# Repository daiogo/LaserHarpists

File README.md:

# What is a laser harp?
A laser harp is a harp that has laser beams emulating the strings of a regular harp. Whenever you intercept a laser beam, a note is played to that correspondent intercepted beam.

# Cool features in our laser harp
- The notes are played by an Android app;
- It's wireless! It communicates with the app via Bluetooth;
- There are ultrasonic range finders that measure the height of your interception;
  - That makes it possible to play 3 notes in a single laser beam.
- There are two modes of operation:
  - Free Play: let your inner Jean Michel Jarre shine (:
  - Learn To Play: learn to play a song in the harp
- RGB LED strips positioned in the front of each laser beam
  - They lit to the note you play when you intercept a laser beam on Free Play mode
  - They lit to the correspondent string and height to be intercepted in the current music

# Pics or it didn't happen
Yes, there's a demo video! Too bad we didn't had the time to learn how to play the harp (:

https://www.youtube.com/watch?v=IKeanOgFvdw

# Bill of materials
- Tiva C Launchpad
- JY-MCU Bluetooth module
- 8 HC-SR04 ultrasonic range finders
- 8 5mW laser diodes
- 8 interception sensors (circuit schematic found inside the repo)
  - comparator IC
  - potentiometer
  - LDR (Light dependent resistor)
  - 0.25W resistors
  - Materials to build a PCB to each interception sensor
- 8 12V RGB LED strips
- 3 high current drivers IC
- 3 shift registers

# Makers
- José Augustinho
  - Firmware programming, PCB confection and project manager
- Rinaldi Segecin
  - Mobile app development, firmware programming
- Diogo Freitas (myself)
  - Hardware development, PCB confection, firmware debugging

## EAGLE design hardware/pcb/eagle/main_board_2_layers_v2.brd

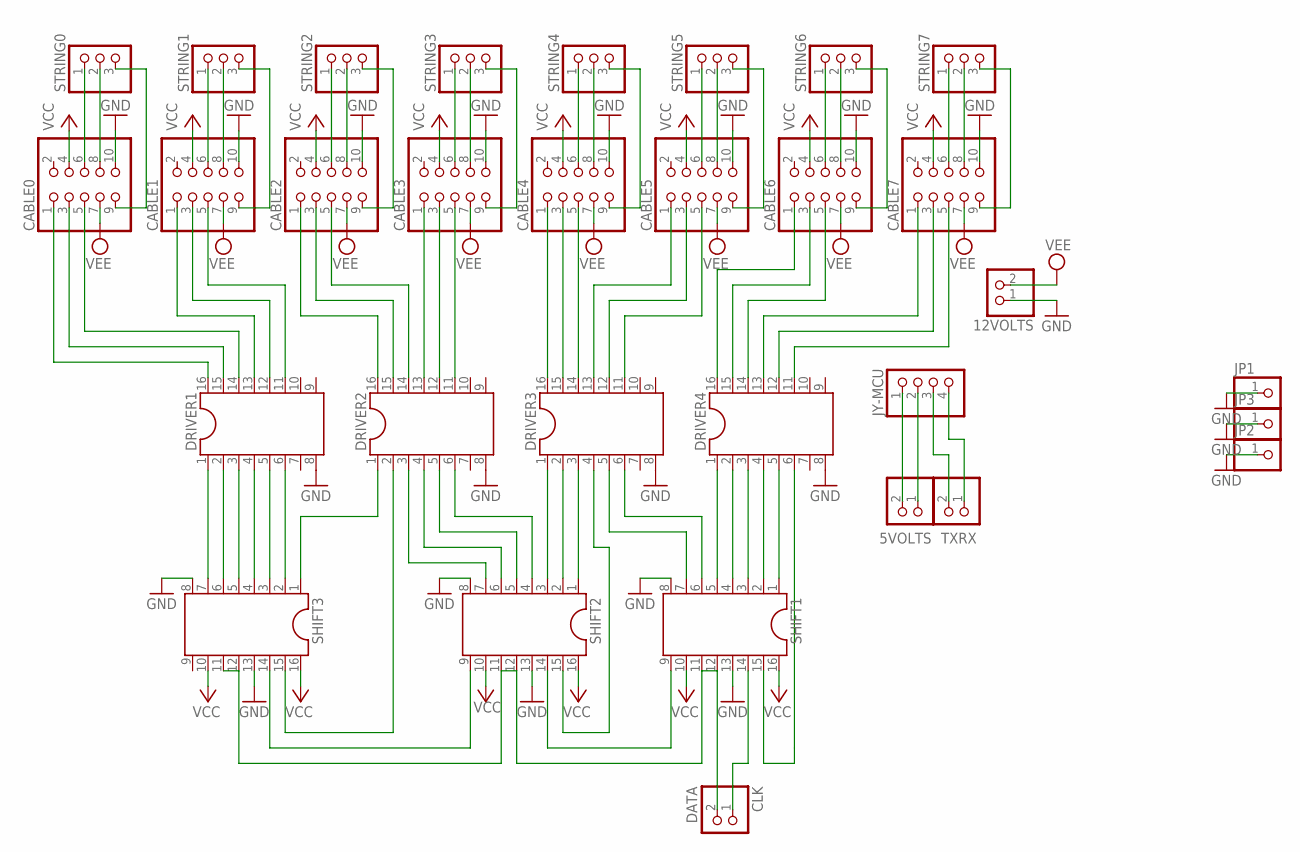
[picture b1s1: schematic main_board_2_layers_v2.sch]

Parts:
5VOLTS, 12VOLTS: PINHD-1X2; 1X02
CABLE0, CABLE1, CABLE2, CABLE3, CABLE4, CABLE5, CABLE6, CABLE7: PINHD-2X5; 2X05
CLK: DATA; 1X02
DRIVER1, DRIVER2, DRIVER3, DRIVER4: DIL16
JP1, JP2, JP3: PINHD-1X1; 1X01
JY-MCU: PINHD-1X4; 1X04
SHIFT1, SHIFT2, SHIFT3: DIL16
STRING0, STRING1, STRING2, STRING3, STRING4, STRING5, STRING6, STRING7: PINHD-1X3; 1X03
TXRX: PINHD-1X2; 1X02

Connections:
GND: 12VOLTS.1, CABLE0.10, CABLE1.10, CABLE2.10, CABLE3.10, CABLE4.10, CABLE5.10, CABLE6.10, CABLE7.10, DRIVER1.8, DRIVER2.8, DRIVER3.8, DRIVER4.8, JP1.1, JP2.1, JP3.1, SHIFT1.8, SHIFT1.13, SHIFT2.8, SHIFT2.13, SHIFT3.8, SHIFT3.13
unnamed: CABLE0.1, DRIVER1.16
unnamed: CABLE0.3, DRIVER1.15
unnamed: CABLE0.5, DRIVER1.14
unnamed: CABLE1.1, DRIVER1.13
unnamed: CABLE1.3, DRIVER1.12
unnamed: CABLE1.5, DRIVER1.11
unnamed: CABLE2.1, DRIVER2.16
unnamed: CABLE2.3, DRIVER2.15
unnamed: CABLE2.5, DRIVER2.14
unnamed: CABLE3.1, DRIVER2.13
unnamed: CABLE3.3, DRIVER2.12
unnamed: CABLE3.5, DRIVER2.11
unnamed: CABLE4.1, DRIVER3.16
unnamed: CABLE4.3, DRIVER3.15
unnamed: CABLE4.5, DRIVER3.14
unnamed: CABLE5.1, DRIVER3.13
unnamed: CABLE5.3, DRIVER3.12
unnamed: CABLE5.5, DRIVER3.11
unnamed: CABLE6.1, DRIVER4.16
unnamed: CABLE6.3, DRIVER4.15
unnamed: CABLE7.1, DRIVER4.13
unnamed: CABLE6.5, DRIVER4.14
unnamed: CABLE7.3, DRIVER4.12
unnamed: CABLE7.5, DRIVER4.11
unnamed: DRIVER4.5, SHIFT1.1
unnamed: DRIVER4.4, SHIFT1.2
unnamed: CABLE1.9, STRING1.3
unnamed: CABLE0.6, STRING0.1
unnamed: CABLE0.9, STRING0.3
unnamed: CABLE0.8, STRING0.2
unnamed: CABLE7.6, STRING7.1
unnamed: CABLE7.8, STRING7.2
unnamed: CABLE1.6, STRING1.1
unnamed: CABLE1.8, STRING1.2
unnamed: CABLE7.9, STRING7.3
unnamed: CABLE2.8, STRING2.2
unnamed: CABLE2.6, STRING2.1
unnamed: CABLE3.9, STRING3.3
unnamed: CABLE3.8, STRING3.2
unnamed: CABLE3.6, STRING3.1
unnamed: CABLE4.9, STRING4.3
unnamed: CABLE4.8, STRING4.2
unnamed: CABLE4.6, STRING4.1
unnamed: CABLE5.9, STRING5.3
unnamed: CABLE5.6, STRING5.1
unnamed: CABLE5.8, STRING5.2
unnamed: CABLE6.9, STRING6.3
unnamed: CABLE6.6, STRING6.1
unnamed: CABLE6.8, STRING6.2
unnamed: DRIVER4.3, SHIFT1.3
unnamed: DRIVER4.2, SHIFT1.4
unnamed: DRIVER4.1, SHIFT1.5
unnamed: DRIVER3.6, SHIFT1.6
unnamed: DRIVER3.5, SHIFT1.7
unnamed: DRIVER3.4, SHIFT2.15
unnamed: DRIVER3.3, SHIFT2.1
unnamed: DRIVER3.2, SHIFT2.2
unnamed: DRIVER3.1, SHIFT2.3
unnamed: DRIVER2.6, SHIFT2.4
unnamed: DRIVER2.5, SHIFT2.5
unnamed: DRIVER2.4, SHIFT2.6
unnamed: DRIVER2.3, SHIFT2.7
unnamed: DRIVER2.2, SHIFT3.15
unnamed: DRIVER2.1, SHIFT3.1
unnamed: DRIVER1.1, SHIFT3.7
unnamed: DRIVER1.2, SHIFT3.6
unnamed: DRIVER1.3, SHIFT3.5
unnamed: DRIVER1.4, SHIFT3.4
unnamed: DRIVER1.5, SHIFT3.3
unnamed: DRIVER1.6, SHIFT3.2
unnamed: 5VOLTS.2, JY-MCU.1
unnamed: 5VOLTS.1, JY-MCU.2
unnamed: JY-MCU.3, TXRX.2
unnamed: SHIFT1.9, SHIFT2.14
unnamed: SHIFT2.9, SHIFT3.14
unnamed: CLK.1, SHIFT1.14
unnamed: CLK.2, SHIFT1.11, SHIFT1.12, SHIFT2.11, SHIFT2.12, SHIFT3.11, SHIFT3.12
unnamed: CABLE2.9, STRING2.3
unnamed: JY-MCU.4, TXRX.1
VCC: CABLE0.4, CABLE1.4, CABLE2.4, CABLE3.4, CABLE4.4, CABLE5.4, CABLE6.4, CABLE7.4, SHIFT1.10, SHIFT1.16, SHIFT2.10, SHIFT2.16, SHIFT3.10, SHIFT3.16
VEE: 12VOLTS.2, CABLE0.7, CABLE1.7, CABLE2.7, CABLE3.7, CABLE4.7, CABLE5.7, CABLE6.7, CABLE7.7

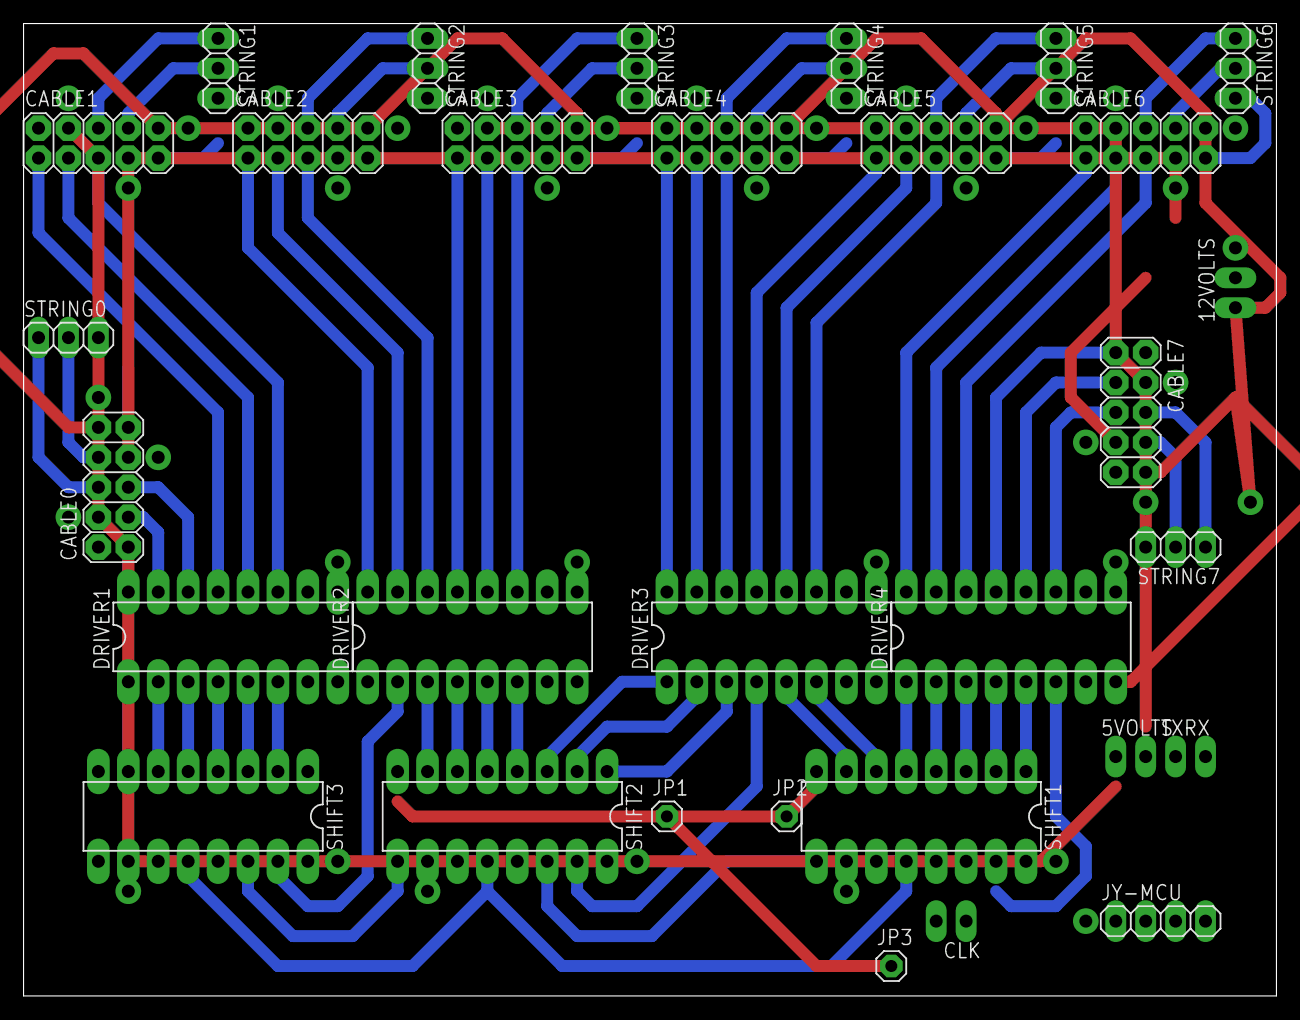
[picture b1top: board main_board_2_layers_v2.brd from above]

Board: 2 copper layers, 106.3 x 82.5 mm, 31 parts (0 on the bottom side), 82 nets.

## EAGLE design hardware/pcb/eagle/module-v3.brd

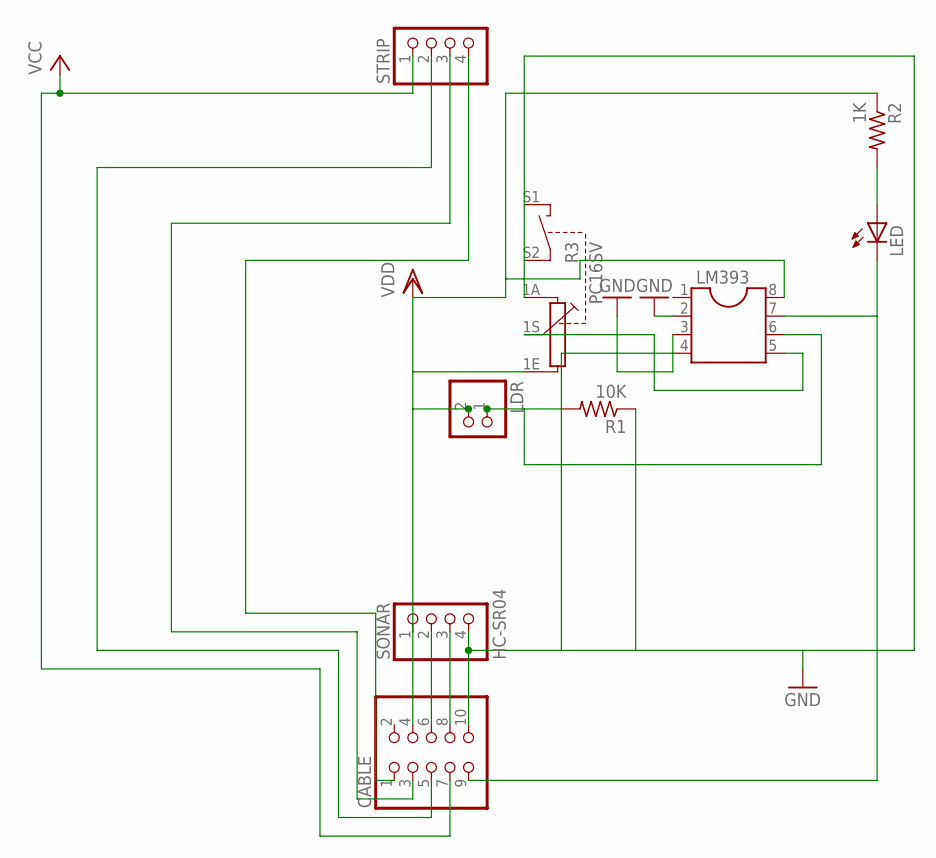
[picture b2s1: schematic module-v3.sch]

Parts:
CABLE: PINHD-2X5; 2X05
LDR: PINHD-1X2-DAIOGO; 1X02
LED: LED3MM
LM393: DIL8; DIL08
R1: 10K; 0207/10
R2: 1K; 0207/10
R3: PC16SV
SONAR: HC-SR04; 1X04
STRIP: PINHD-1X4; 1X04

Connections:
GND: CABLE.10, LM393.2, LM393.3, LM393.4, R1.1, R3.1A, SONAR.4
unnamed: LM393.5, R3.1S
unnamed: LDR.1, LM393.6, R1.2
unnamed: LED.A, R2.2
unnamed: CABLE.9, LED.K (C), LM393.7
unnamed: CABLE.8, SONAR.3
unnamed: CABLE.6, SONAR.2
unnamed: CABLE.1, STRIP.4
unnamed: CABLE.3, STRIP.3
unnamed: CABLE.5, STRIP.2
VCC: CABLE.7, STRIP.1
VDD: CABLE.4, LDR.2, LM393.8, R2.1, R3.1E, SONAR.1

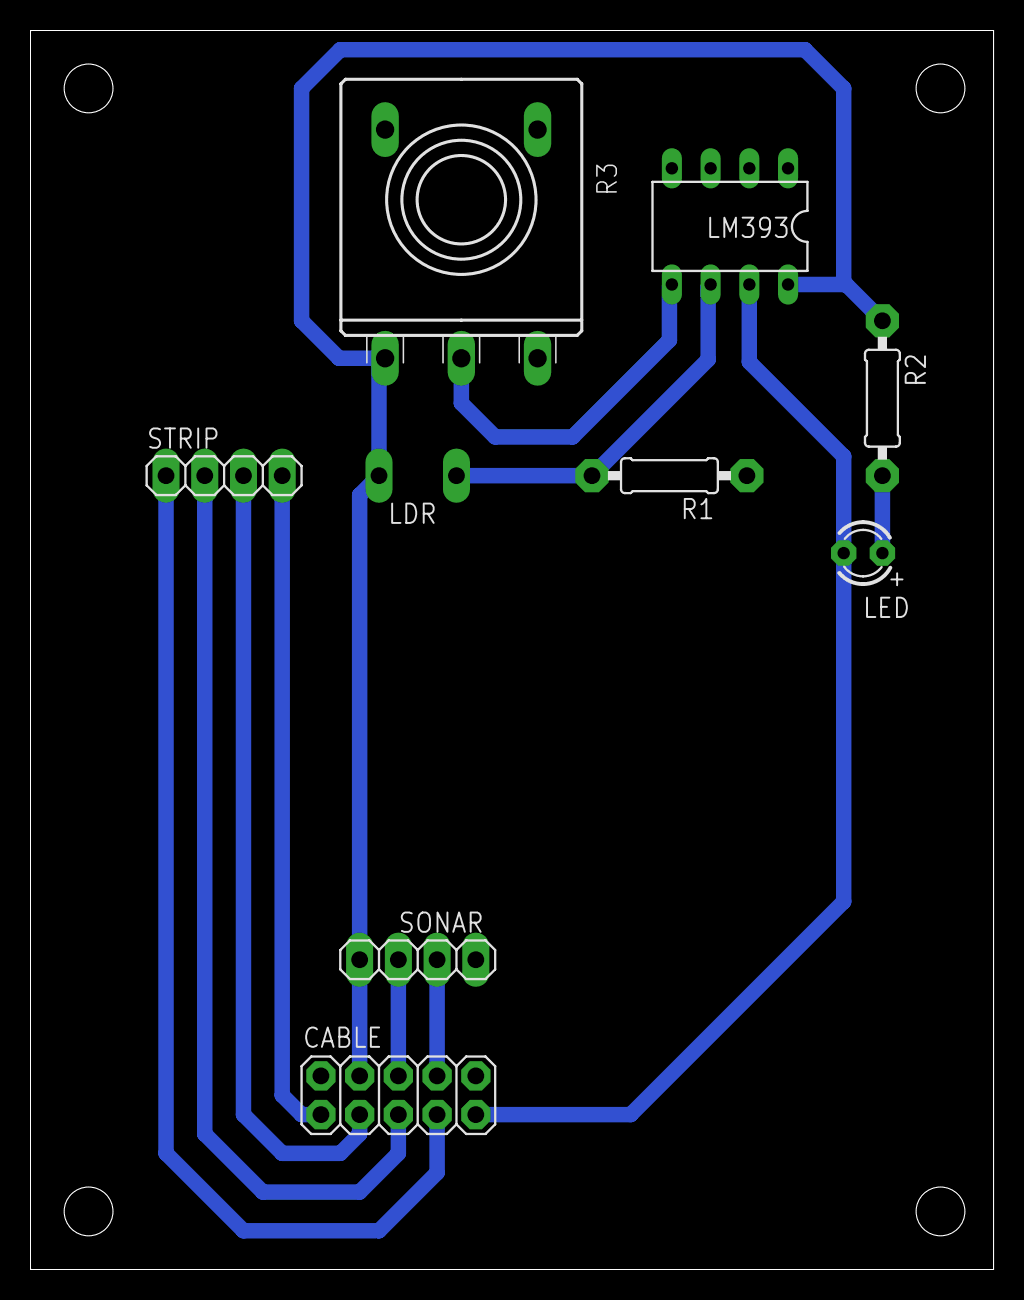
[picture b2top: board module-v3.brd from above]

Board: 2 copper layers, 63.2 x 81.3 mm, 9 parts (0 on the bottom side), 12 nets.

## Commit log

2015-12-15 version 1.0
